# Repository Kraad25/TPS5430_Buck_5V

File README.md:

# TPS5430_Buck_5V

A 12V-to-5V synchronous buck converter built around the TI TPS54308, designed in
KiCad.

Schematic and component values derived directly from the TPS54308 datasheet.

## Specs

- **Controller:** TPS54308 (4.5V-28V input, 3A synchronous buck converter, SOT-23-6)
- **Input:** 12V DC via barrel jack
- **Output:** 5V, 3A via 2-pin header
- **Switching frequency:** 350kHz (fixed, internal)
- **Layers:** 2-layer
- **Note:** Found and corrected a unit typo in the datasheet's Table 7-2 (C6
  listed as µF, confirmed via TI's own body text and the compensation equation
  to actually be pF)

## PCB Design

### Schematic

### PCB Layout

### 3D Renders

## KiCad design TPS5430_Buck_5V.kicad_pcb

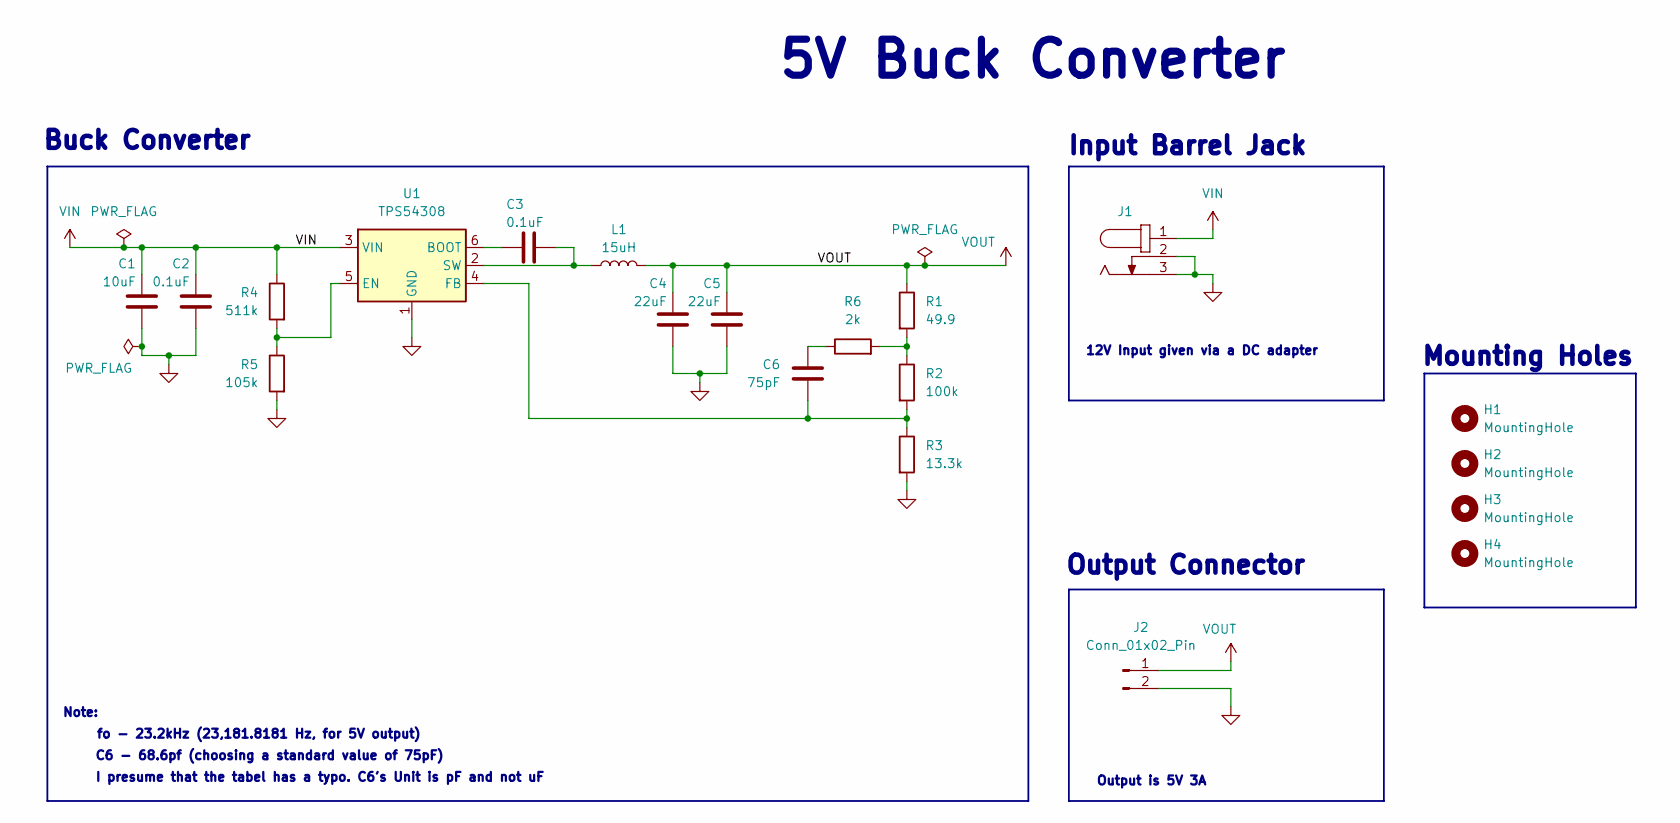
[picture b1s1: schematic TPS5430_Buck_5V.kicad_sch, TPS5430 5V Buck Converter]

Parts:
C1: 10uF; C_0805_2012Metric
C2, C3: 0.1uF; C_0805_2012Metric
C4, C5: 22uF; C_0805_2012Metric
C6: 75pF; C_0805_2012Metric
H1, H2, H3, H4: MountingHole; MountingHole_2.2mm_M2_ISO7380
J1: 694103107102; J_Wurth_WR-DC_694103107102; Working Voltage (V (DC)) 24; Part Number 694103107102
J2: Conn_01x02_Pin; PinHeader_1x02_P2.00mm_Vertical
L1: 15uH; L_1008_2520Metric
R1: 49.9; R_0805_2012Metric
R2: 100k; R_0805_2012Metric
R3: 13.3k; R_0805_2012Metric
R4: 511k; R_0805_2012Metric
R5: 105k; R_0805_2012Metric
R6: 2k; R_0805_2012Metric
U1: TPS54308; SOT-23-6

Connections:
GND: C1.1, C2.1, C4.1, C5.1, J1.2, J1.3, J2.2, R3.2, R5.2, U1.1 (GND)
unnamed: C6.2, R6.1
unnamed: R1.2, R2.1, R6.2
unnamed: C3.2, U1.6 (BOOT)
unnamed: R4.2, R5.1, U1.5 (EN)
unnamed: C6.1, R2.2, R3.1, U1.4 (FB)
unnamed: C3.1, L1.1, U1.2 (SW)
VIN: C1.2, C2.2, J1.1, R4.1, U1.3 (VIN)
VOUT: C4.2, C5.2, J2.1, L1.2, R1.1

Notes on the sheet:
Mounting Holes
Buck Converter
Output Connector
I presume that the tabel has a typo. C6's Unit is pF and not uF
12V Input given via a DC adapter
fo - 23.2kHz (23,181.8181 Hz, for 5V output)
Note:
C6 - 68.6pf (choosing a standard value of 75pF)
5V Buck Converter
Input Barrel Jack
Output is 5V 3A

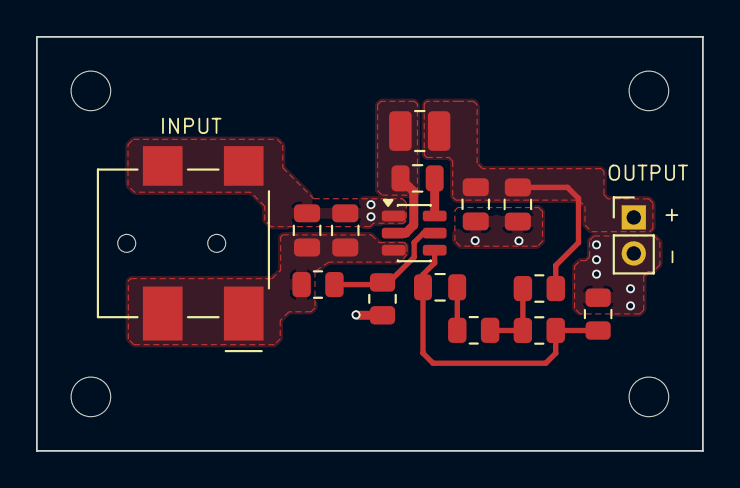
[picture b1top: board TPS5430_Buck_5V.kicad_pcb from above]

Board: 2 copper layers, 37.0 x 23.0 mm, 20 parts (0 on the bottom side), 9 nets.
